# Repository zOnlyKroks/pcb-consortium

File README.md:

# PCB / Circuit Designs

## Support & Issues
If something is broken, unclear, or you need help assembling:
- Open a GitHub Issue
- I’ll try to help when I can

Use at your own risk 🙂

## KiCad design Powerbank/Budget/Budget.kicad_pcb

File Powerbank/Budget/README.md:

# Budget 18650 Powerbank

1S powerbank with 4x 18650 in parallel (about 40-50 Wh with 3.0-3.4 Ah cells). One highly integrated SoC (SW6106) does the charging, the boost and the USB protocols. Built for JLCPCB economic assembly, all parts on the top side.

**Status:** schematic done (ERC 0 violations, netlist matches an independent net spec, 41/41 nets). Board is **placed, not routed** (130 x 90 mm, 2 layers). DRC shows 0 errors other than the unrouted ratsnest, and schematic parity is 0.

## Architecture

| Block | Parts | Notes |
|---|---|---|
| Power SoC | SW6106 (iSmartware) | 4 A switch-mode charger, 18 W synchronous boost, PD3.0 / QC3.0 / AFC / FCP / PE / SFCP out, PD / AFC / FCP in, 4-LED gauge, key input |
| Ports | USB-C (J1) + USB-A (J2) | Each has an AO3420 power-path switch (Q4/Q5) driven by the SoC. USB-C does PD in and out; USB-A is QC/AFC/FCP out only. Micro-B is not used (VBUS_B tied to GND, GATE_B/DPB/DMB open). |
| Power stage | L1 2.2 uH, R1 5 mOhm shunt, C1-C4, C7-C10 | Follows the SW6106 typical application circuit |
| Cell protection | DW01A + 3x FS8205A in parallel | The SW6106 has no cell protection of its own (only a 2.9 V UVLO). Each FS8205A is two FETs in series (about 50 mOhm), so three in parallel are about 17 mOhm, and the DW01A overcurrent trip (about 0.15 V) lands near 9 A. Boost peak at 18 W and 3.0 V is about 6.7 A. |
| Gauge | D1-D4 (charlieplex on LED1-3), D5 fast-charge LED | Press SW1 to show the level |
| NTC | RT1 10k (B3380) | Charge and boost temperature protection. Place it touching a cell. |

Output: 5 V / 3 A, 9 V / 2 A, 12 V / 1.5 A (18 W max). Both ports on at once give 5 V only. Charging: 5 V in = 2.5 A, 9 V / 12 V in = 4 A to the pack (4 A = 0.33 C with 4 cells).

Ground naming: `GND` = PACK- (system ground, after the protection FETs); `CELL_N` = cell stack bottom (DW01A VSS); `VBAT` = cell +.

## Things to check before ordering

- **SW6106 reference circuit.** The typical-application figure in DS008 v2.2 is low resolution. The 100 nF across the shunt, the 22 uF caps at the inductor node / BAT / VOUT, the 1 uF VDRV and the 10 uF VCC are read from the block diagram and figure. Compare them with the official reference design from iSmartware.
- **LED charlieplex order.** LED1-4 are wired per the 4-LED figure in the datasheet. If the bar lights in the wrong order or one LED is dark, swap the polarity of that LED.
- **USB-A part C42570 (JTJ USB-AF-10.0-032).** The footprint is the EasyEDA one: SMD signal pads, through-hole shield legs. Confirm JLC economic assembly accepts it (or hand-solder the legs). The USB-C (C165948) also has through-hole shield legs.
- **Basic vs extended.** Not verified (no JLC parts API access here). The SoC, DW01A, FS8205A, AO3420, inductor, shunt, both USB connectors, holder and switch are almost certainly extended parts (about 3 USD each on economic). The 0603/0805/1206 passives were taken from the V2 BOM, which was checked on 2026-10-24.
- **AO3420 (C358680).** Listed as AOS, marked "not for new designs" at DigiKey. Fallback: MSKSEMI AO3420 C5379109 (18 mOhm), same footprint.
- **CPL rotations** need the usual JLC correction pass (QFN, TSSOP, SOT-23, USB connectors); I did not generate a CPL.
- **Cells.** All four are in parallel with no per-cell protection. Insert cells at the same voltage, same type, and ideally from the same batch. A per-cell fuse is not fitted (budget).

## Board

- 130 x 90 mm, 2 layers, 4 holders on the left (all + up, so VBAT is the top bus and CELL_N the bottom bus), electronics on the right strip, USB ports on the right edge with the gauge LEDs and key beside them.
- Mounting holes: 4x M3 (H1-H4). H1/H2 sit between the holders and the electronics.
- Layers / stackup: 2 copper layers (F.Cu, B.Cu), JLC 1.6 mm FR4, 1 oz (35 um) copper, HASL. B.Cu carries a GND pour (0.3 mm clearance, thermal reliefs, 0.5 mm from the edge). Economic assembly is single-sided, so all parts are on F.Cu and B.Cu is routing + ground.
- Net classes: `Default` 0.25 mm track / 0.2 mm clearance / via 0.6 / 0.3 drill; `Power` (GND, VOUT, VBUS_x switch nodes, SW, BATCSP) 0.8 mm track / via 0.8 / 0.4; `HighCurrent` (VBAT, CELL_N) 2.0 mm track / via 1.0 / 0.5. Use pours where a 2 mm track does not fit.
- Predefined track widths (mm): 0.15, 0.2, 0.25, 0.3, 0.4, 0.5, 0.8, 1.0, 1.5, 2.0, 3.0. Predefined vias (pad / drill): 0.6 / 0.3, 0.8 / 0.4, 1.0 / 0.5.
- Design rules (JLC 2-layer): min clearance 0.1, track 0.15, via 0.6 / 0.3 (0.15 annular), copper to edge 0.3, hole to hole 0.5, silk text 1.0 mm high / 0.15 thick.
- The USB-C footprint has pads 0.1 mm apart (inherent to the part); the J1 pads carry a 0.09 mm local clearance.
- U1: the four thermal vias share pad 41 (GND). Fill the EP with the planned via pattern when routing.

### Routing notes (for later)

- **High current** (about 6-9 A): VBAT bus (holder tops -> R1 -> U1 BAT), CELL_N bus (holder bottoms -> Q1-Q3 S1 pins), Q1-Q3 S2 to GND, and VOUT to Q4/Q5. Use wide copper or pours.
- **GND:** the second layer is meant as a GND plane with vias at U1 EP and the FET sources.
- **SW6106:** keep the SW-L1 loop (L1 above U1) and C1 (BST) tight; C7-C10 close to the VOUT pads.
- **Shunt R1:** route BATCSP/BAT Kelvin from the pads; C3 sits at the pads.
- **Q1-Q3:** the three FS8205A share OD (gate 1) and OC (gate 2) nets from U2; keep those short.
- **DW01A:** R2 (VM) goes to GND, C13 (VCC to CELL_N) right at U2.

## Files

- `Budget.kicad_sch` single-sheet schematic, `Budget.kicad_pcb` placed board
- `lib/Budget.kicad_sym`, `lib/Budget.pretty` project symbols and footprints (SW6106, DW01A, FS8205A, USB, holder, inductor, ...)
- `jlcpcb/BOM-Budget.csv` BOM with LCSC numbers (38 parts, 20 unique)

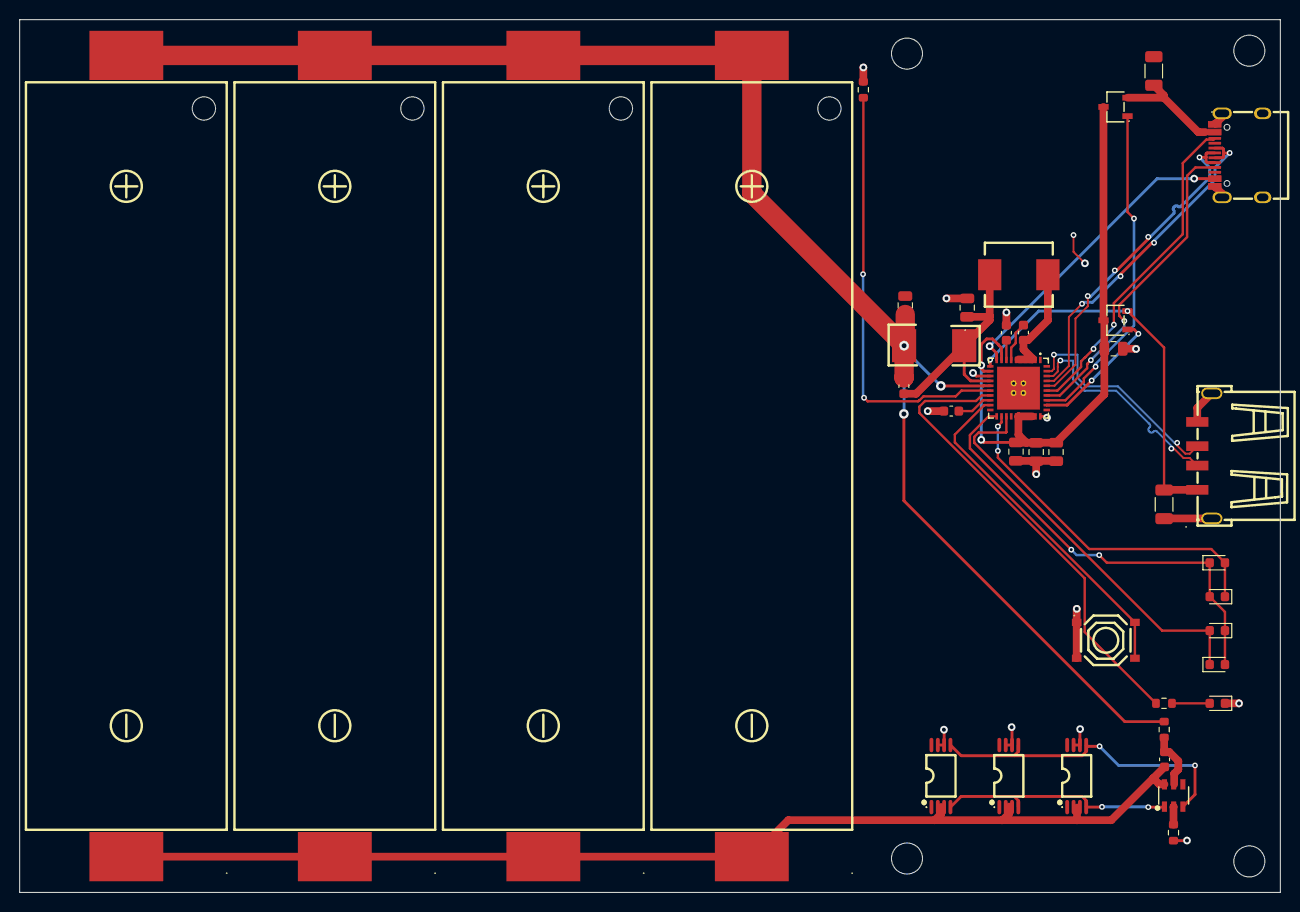
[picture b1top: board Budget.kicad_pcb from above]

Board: 2 copper layers, 130.0 x 90.0 mm, 42 parts (0 on the bottom side), 30 nets.

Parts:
BT1, BT2, BT3, BT4: 18650; BatteryHolder_BH-18650-B1BA002
C1, C3, C13: 100nF; C_0603_1608Metric
C2, C4, C7, C8, C9, C10: 22uF; C_0805_2012Metric
C5: 1uF; C_0603_1608Metric
C6: 10uF; C_0603_1608Metric
C11, C12: 10uF 50V; C_1206_3216Metric
D1, D2, D3, D4: LED; LED_0603_1608Metric
D5: CHG; LED_0603_1608Metric
H1, H2, H3, H4: M3; MountingHole_3.2mm_M3
J1: USB-C; USB-C_SMD-TYPE-C-31-M-12_1
J2: USB-A; USB-A-SMD_JTJ-USB-AF-10.0-032
L1: 2.2uH; L_7.0x6.6_MWSA0603S
Q1, Q2, Q3: FS8205A; TSSOP-8_L4.4-W3.0-P0.65-LS6.4-BL-2
Q4, Q5: AO3420; SOT-23-3_L2.9-W1.6-P1.90-LS2.8-BR
R1: 5mR 1%; RES-SMD_L6.4-W3.2-1
R2, R4: 2.2k; R_0603_1608Metric
R3: 100R; R_0603_1608Metric
RT1: 10k B3380; R_0603_1608Metric
SW1: KEY; SW_TS-1187A_5.1x5.1
U1: SW6106; QFN-40_L6.0-W6.0-P0.50-BL-EP
U2: DW01A; SOT-23-6_L2.9-W1.6-P0.95-LS2.8-BL

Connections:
/A_D+: J2.3 (D+), U1.39 (DPA)
/A_D-: J2.2 (D-), U1.38 (DMA)
/C_D+: J1.A6 (D+), J1.B6 (D+), U1.37 (DPC)
/C_D-: J1.A7 (D-), J1.B7 (D-), U1.36 (DMC)
CELL_N: BT1.2 (-), BT2.2 (-), BT3.2 (-), BT4.2 (-), C13.2, Q1.2 (S1), Q1.3 (S1), Q2.2 (S1), Q2.3 (S1), Q3.2 (S1), Q3.3 (S1), U2.6 (GND)
GND: C2.2, C4.2, C5.1, C6.1, C7.2, C8.2, C9.2, C10.2, C11.2, C12.2, D5.1 (K), J1.1 (GND), J1.2 (GND), J1.3 (GND), J1.4 (GND), J1.A1B12 (GND), J1.B1A12 (GND), J2.4 (GND), J2.5 (SH), J2.6 (SH), Q1.6 (S2), Q1.7 (S2), Q2.6 (S2), Q2.7 (S2), Q3.6 (S2), Q3.7 (S2), R2.2, RT1.1, SW1.1 (A), SW1.3 (A), U1.13 (AGND), U1.30 (VBUS_B), U1.41 (EPAD)
unnamed: C1.2, L1.2, U1.2 (SW), U1.3 (SW), U1.4 (SW), U1.5 (SW), U1.6 (SW)
unnamed: D1.2 (A), D2.1 (K), U1.22 (LED2_SDA)
unnamed: D1.1 (K), D2.2 (A), D3.1 (K), D4.2 (A), U1.21 (LED1_SCK)
unnamed: D3.2 (A), D4.1 (K), U1.23 (LED3_IRQ)
unnamed: D5.2 (A), R4.1
unnamed: J1.A5 (CC1), U1.34 (CC1)
unnamed: J1.B5 (CC2), U1.35 (CC2)
unnamed: C12.1, J2.1 (VBUS), Q5.2 (S), U1.11 (VBUS_A)
unnamed: Q1.4 (G1), Q2.4 (G1), Q3.4 (G1), U2.1 (OD)
unnamed: Q1.5 (G2), Q2.5 (G2), Q3.5 (G2), U2.3 (OC)
unnamed: Q4.1 (G), U1.33 (GATE_C)
unnamed: C11.1, J1.A4B9 (VBUS), J1.B4A9 (VBUS), Q4.2 (S), U1.10 (VBUS_C)
unnamed: Q5.1 (G), U1.32 (GATE_A)
unnamed: C2.1, C3.1, L1.1, R1.1, U1.14 (BATCSP)
unnamed: R4.2, U1.17 (BSET_HLED)
unnamed: C1.1, U1.7 (BST)
unnamed: SW1.2 (B), SW1.4 (B), U1.19 (KEY)
unnamed: RT1.2, U1.16 (NTC)
unnamed: C6.2, U1.18 (VCC)
unnamed: C5.2, U1.8 (VDRV)
unnamed: C13.1, R3.2, U2.5 (VCC)
unnamed: R2.1, U2.2 (VM)
VBAT: BT1.1 (+), BT2.1 (+), BT3.1 (+), BT4.1 (+), C3.2, C4.1, R1.2, R3.1, U1.15 (BAT)
VOUT: C7.1, C8.1, C9.1, C10.1, Q4.3 (D), Q5.3 (D), U1.9 (VOUT_C), U1.12 (VOUT_A), U1.25 (VOUT), U1.26 (VOUT), U1.27 (VOUT), U1.28 (VOUT), U1.29 (VOUT)

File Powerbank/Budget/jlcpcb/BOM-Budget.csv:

Comment,Designator,Footprint,LCSC Part #,Quantity
18650,"BT1,BT2,BT3,BT4",BatteryHolder_BH-18650-B1BA002,C2988620,4
100nF,"C1,C3,C13",C_0603_1608Metric,C14663,3
22uF,"C2,C4,C7,C8,C9,C10",C_0805_2012Metric,C45783,6
1uF,C5,C_0603_1608Metric,C15849,1
10uF,C6,C_0603_1608Metric,C19702,1
10uF 50V,"C11,C12",C_1206_3216Metric,C13585,2
LED,"D1,D2,D3,D4",LED_0603_1608Metric,C2290,4
CHG,D5,LED_0603_1608Metric,C2286,1
USB-C,J1,USB-C_SMD-TYPE-C-31-M-12_1,C165948,1
USB-A,J2,USB-A-SMD_JTJ-USB-AF-10.0-032,C42570,1
2.2uH,L1,L_7.0x6.6_MWSA0603S,C408445,1
FS8205A,"Q1,Q2,Q3",TSSOP-8_L4.4-W3.0-P0.65-LS6.4-BL-2,C14212,3
AO3420,"Q4,Q5",SOT-23-3_L2.9-W1.6-P1.90-LS2.8-BR,C358680,2
5mR 1%,R1,RES-SMD_L6.4-W3.2-1,C2903482,1
2.2k,"R2,R4",R_0603_1608Metric,C4190,2
100R,R3,R_0603_1608Metric,C22775,1
10k B3380,RT1,R_0603_1608Metric,C13564,1
KEY,SW1,SW_TS-1187A_5.1x5.1,C318884,1
SW6106,U1,QFN-40_L6.0-W6.0-P0.50-BL-EP,C406803,1
DW01A,U2,SOT-23-6_L2.9-W1.6-P0.95-LS2.8-BL,C351410,1

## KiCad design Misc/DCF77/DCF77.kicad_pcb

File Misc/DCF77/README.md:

# DCF77 Receiver (self-tuning)

An open-source receiver for the 77.5 kHz DCF77 time signal. Only the ferrite antenna is external, and the board tunes its resonance itself, so a home-wound antenna does not have to hit its inductance exactly. An STM32F103 samples the amplified carrier, demodulates it with a Goertzel filter and decodes the time. The result goes out over USB (virtual COM port), I²C, SPI or UART, with a one-pulse-per-second TICK and the raw pulse.

```
ferrite rod ──┬── tank node ── TLV9062 (x11) ── TLV9062 (x9.2) ── MCU ADC
 (L ≈ 10 mH)  │
              ├── 330 pF fixed C0G
              ├── 10/15/27/56 pF C0G bank via 74HC4066   coarse, 16 steps
              ├── 1SV281 varactor ← MCP4725 DAC          fine
              └── 2.2 pF ← MCU PWM tone                  calibration without a signal
```

**Tuning loop:** sweep the 16 bank codes, climb on the DAC to the carrier peak, then track. Re-sweep on signal loss.

## How far can the antenna be off?

The tuner covers a total tank capacitance of 365–494 pF: 330 pF fixed, 25 pF assumed stray, 0–108 pF bank and about 10–31 pF varactor. At 77.5 kHz that means:

| | Inductance | Versus 10 mH |
|---|---|---|
| Lowest the tuner can reach | 8.5 mH | −15 % |
| Highest the tuner can reach | 11.6 mH | +16 % |

- **Winding:** aim for 10 mH. Inductance goes with turns squared, so the turn count can be off by about ±6 %.
- **Temperature:** drift of about ±1 % uses part of the margin, so staying within 9–11 mH keeps it.
- **Self-capacitance:** the 25 pF stray figure includes the winding's own capacitance. A winding with much more (typically a multi-layer one) shifts the window down. Measure the finished antenna if you can.
- **Q:** the analysis assumes Q = 150. The switches and bias resistor reduce it to 110–135, giving 570–710 Hz bandwidth, enough for the 100/200 ms pulses. The tuner only fixes the frequency, so a low-Q winding still loses signal.
- **Resolution:** the varactor span (21 pF) is larger than the largest coarse step (10 pF), so there are no gaps. One DAC step moves the resonance by about 0.1 Hz.

These figures come from `analysis/frontend.py` (`python3 -I analysis/frontend.py`). The varactor curve is fitted to the 1SV281's distributor figures (8.7 pF at 4 V, ratio 2.0), not its datasheet curve, so treat the window edges as roughly ±1 % uncertain.

## Simulation

The Analog sheet simulates in KiCad (Inspect > Simulator), with models in `models/`. Use `.tran 0.5u 200m` without `uic`. The antenna carrier is keyed like DCF77 (`tred` on J1: 100m for a 0, 200m for a 1). The MCU and power sheets are excluded.

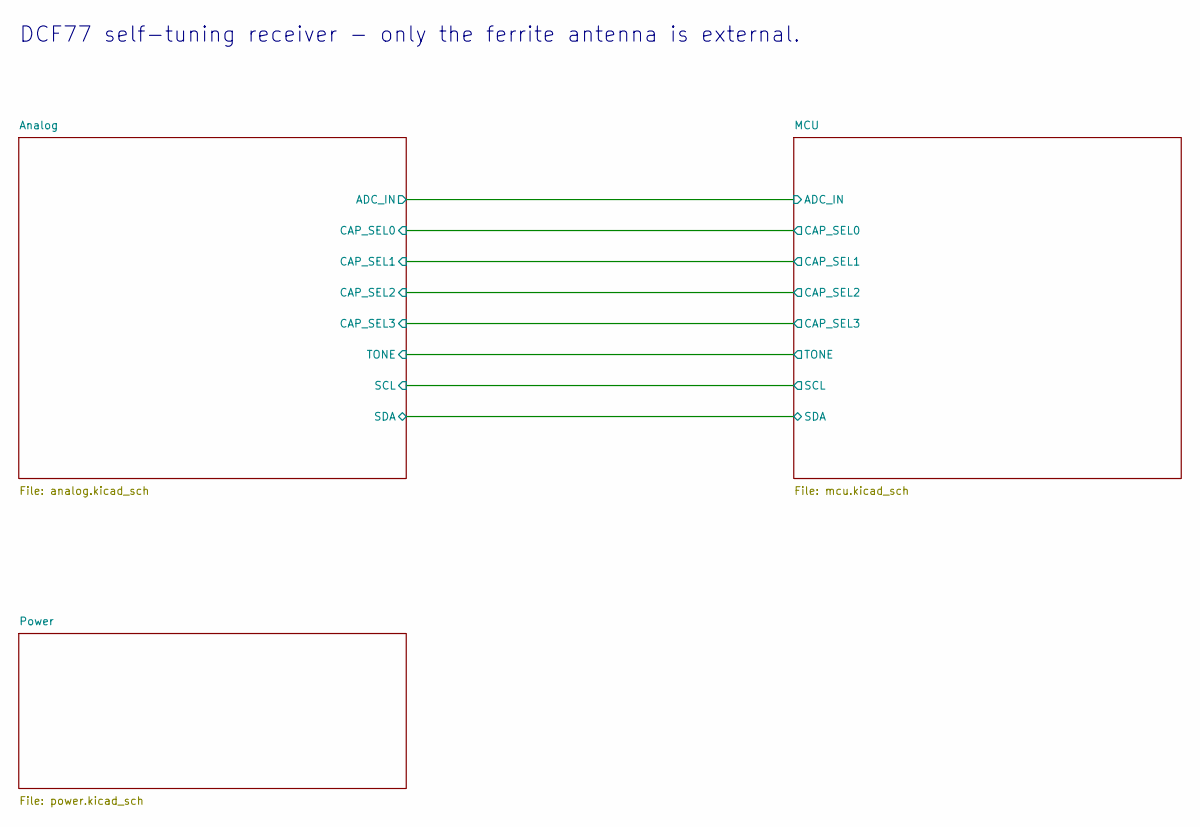
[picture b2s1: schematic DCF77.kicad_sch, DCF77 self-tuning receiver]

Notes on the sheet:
DCF77 self-tuning receiver - only the ferrite antenna is external.

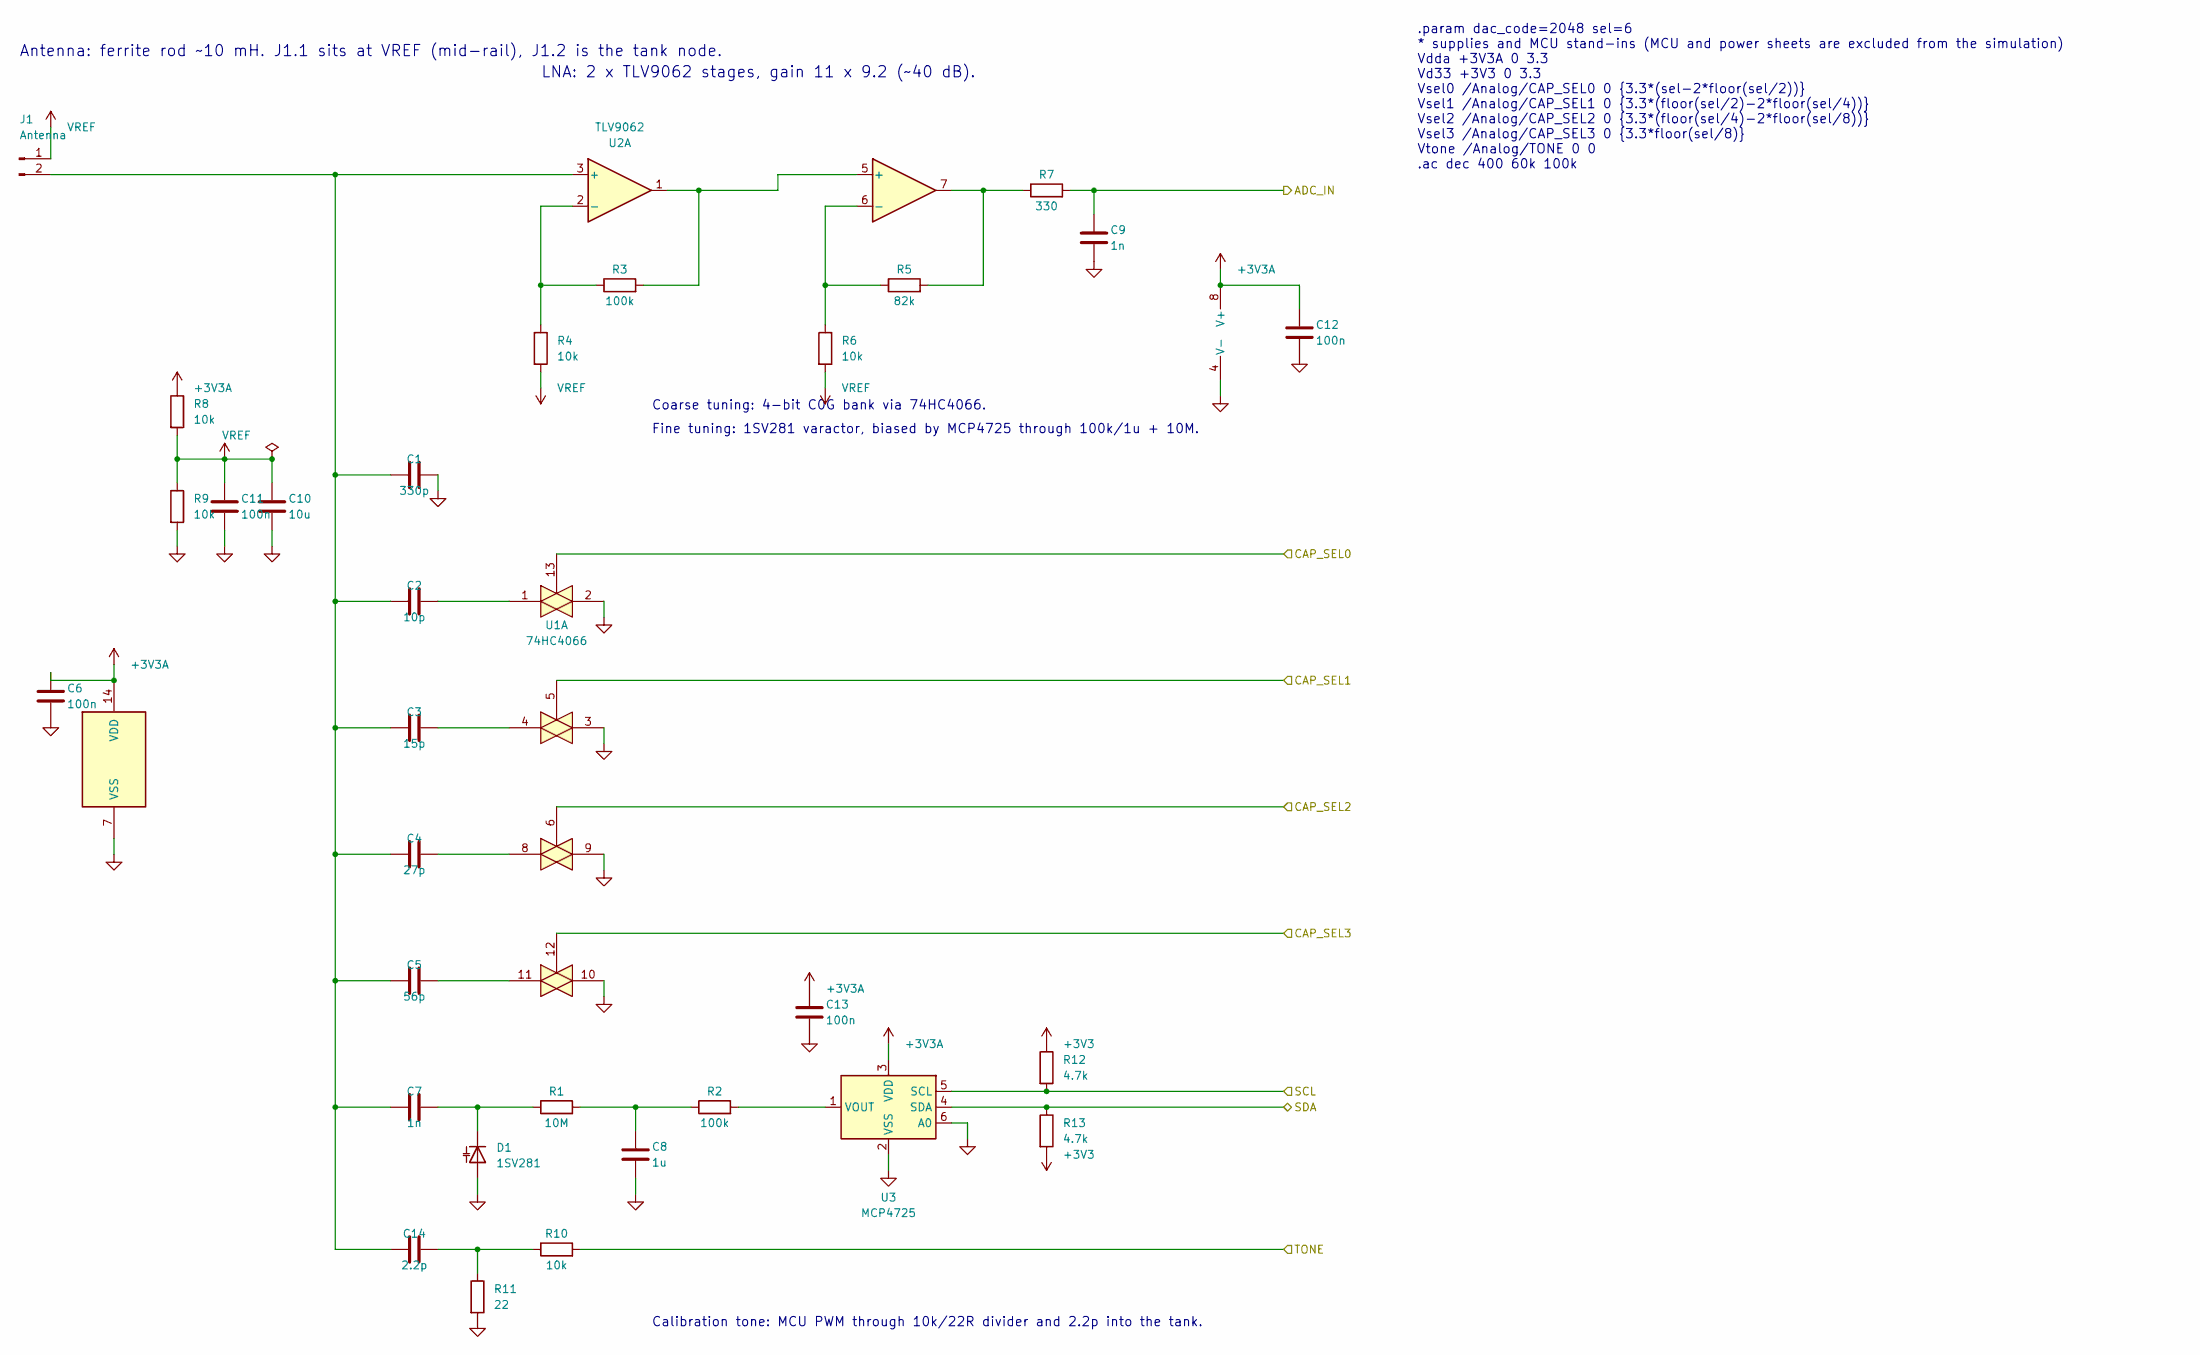
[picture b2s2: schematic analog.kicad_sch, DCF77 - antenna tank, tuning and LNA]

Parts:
C1: 330p; C_0603_1608Metric; LCSC C1664
C2: 10p; C_0603_1608Metric; LCSC C91367
C3: 15p; C_0603_1608Metric; LCSC C1644
C4: 27p; C_0603_1608Metric; LCSC C1656
C5: 56p; C_0603_1608Metric; LCSC C282507
C6, C11, C12, C13: 100n; C_0603_1608Metric; LCSC C14663
C7, C9: 1n; C_0603_1608Metric; LCSC C1636
C8: 1u; C_0603_1608Metric; LCSC C59782
C10: 10u; C_0805_2012Metric; LCSC C15850
C14: 2.2p; C_0603_1608Metric; LCSC C1651
D1: 1SV281; D_SOD-523; LCSC C146317
J1: Antenna; PinHeader_1x02_P2.54mm_Vertical; LCSC C22373836
R1: 10M; R_0603_1608Metric; LCSC C7250
R2, R3: 100k; R_0603_1608Metric; LCSC C25803
R4, R6, R8, R9, R10: 10k; R_0603_1608Metric; LCSC C25804
R5: 82k; R_0603_1608Metric; LCSC C202957
R7: 330; R_0603_1608Metric; LCSC C23138
R11: 22; R_0603_1608Metric; LCSC C23345
R12, R13: 4.7k; R_0603_1608Metric; LCSC C23162
U1: 74HC4066; SOIC-14_3.9x8.7mm_P1.27mm; LCSC C5628
U2: TLV9062; SOIC-8_3.9x4.9mm_P1.27mm; LCSC C398355
U3: MCP4725; SOT-23-6; LCSC C144198

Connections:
+3V3: R12.1, R13.2; also elsewhere on the board
+3V3A: C6.1, C12.1, C13.1, R8.1, U1.14 (VDD), U2.8 (V+), U3.3 (VDD); also elsewhere on the board
/Analog/ADC_IN: C9.1, R7.2; also elsewhere on the board
/Analog/CAP_SEL0: U1.13; also elsewhere on the board
/Analog/CAP_SEL1: U1.5; also elsewhere on the board
/Analog/CAP_SEL2: U1.6; also elsewhere on the board
/Analog/CAP_SEL3: U1.12; also elsewhere on the board
/Analog/SCL: R12.2, U3.5 (SCL); also elsewhere on the board
/Analog/SDA: R13.1, U3.4 (SDA); also elsewhere on the board
/Analog/TONE: R10.2; also elsewhere on the board
GND: C1.2, C6.2, C8.2, C9.2, C10.2, C11.2, C12.2, C13.2, D1.2 (A), R9.2, R11.2, U1.2, U1.3, U1.7 (VSS), U1.9, U1.10, U2.4 (V-), U3.2 (VSS), U3.6 (A0); also elsewhere on the board
unnamed: C2.2, U1.1
unnamed: C3.2, U1.4
unnamed: C4.2, U1.8
unnamed: C5.2, U1.11
unnamed: C8.1, R1.2, R2.1
unnamed: C14.2, R10.1, R11.1
unnamed: C7.2, D1.1 (K), R1.1
unnamed: C1.1, C2.1, C3.1, C4.1, C5.1, C7.1, C14.1, J1.2, U2.3 (+)
unnamed: R5.2, R7.1, U2.7
unnamed: R3.1, R4.1, U2.2 (-)
unnamed: R3.2, U2.1, U2.5 (+)
unnamed: R5.1, R6.1, U2.6 (-)
unnamed: R2.2, U3.1 (VOUT)
VREF: C10.1, C11.1, J1.1, R4.2, R6.2, R8.2, R9.1

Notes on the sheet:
Antenna: ferrite rod ~10 mH. J1.1 sits at VREF (mid-rail), J1.2 is the tank node.
Calibration tone: MCU PWM through 10k/22R divider and 2.2p into the tank.
.param dac_code=2048 sel=6 * supplies and MCU stand-ins (MCU and power sheets are excluded from the simulation) Vdda +3V3A 0 3.3 Vd33 +3V3 0 3.3 Vsel0 /Analog/CAP_SEL0 0 {3.3*(sel-2*floor(sel/2))} Vsel1 /Analog/CAP_SEL1 0 {3.3*(floor(sel/2)-2*floor(sel/4))} Vsel2 /Analog/CAP_SEL2 0 {3.3*(floor(sel/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
Fine tuning: 1SV281 varactor, biased by MCP4725 through 100k/1u + 10M.
Coarse tuning: 4-bit C0G bank via 74HC4066.
LNA: 2 x TLV9062 stages, gain 11 x 9.2 (~40 dB).

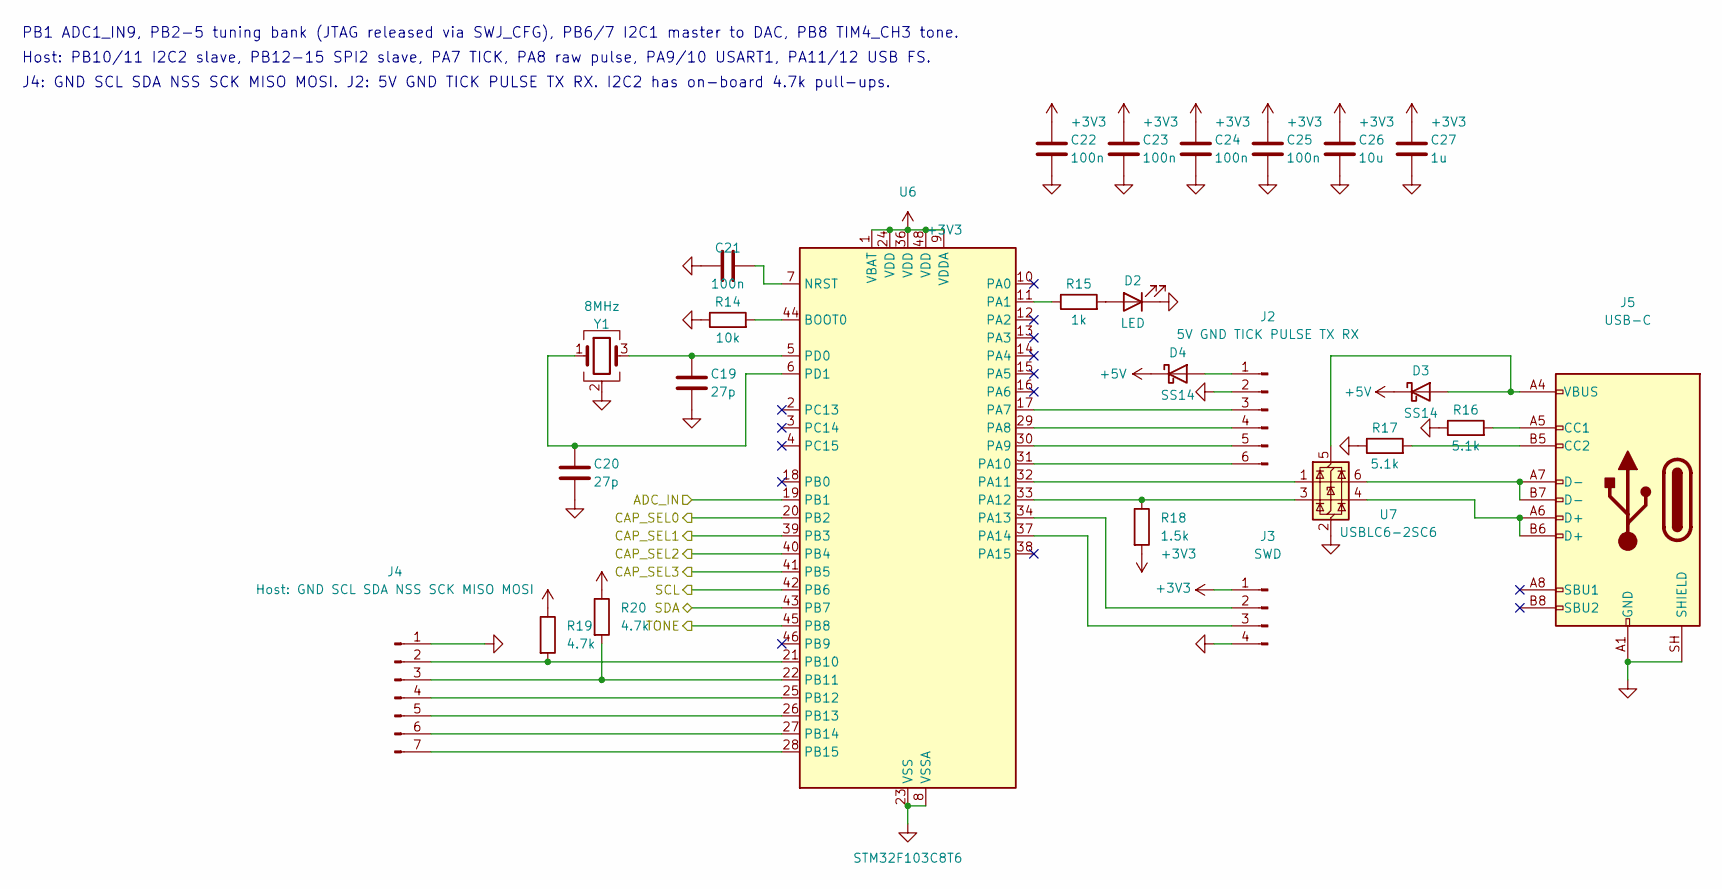
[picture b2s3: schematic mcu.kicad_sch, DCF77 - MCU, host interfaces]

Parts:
C19, C20: 27p; C_0603_1608Metric; LCSC C1656
C21, C22, C23, C24, C25: 100n; C_0603_1608Metric; LCSC C14663
C26: 10u; C_0805_2012Metric; LCSC C15850
C27: 1u; C_0603_1608Metric; LCSC C59782
D2: LED; LED_0603_1608Metric; LCSC C2286
D3, D4: SS14; D_SMA; LCSC C2480
J2: 5V GND TICK PULSE TX RX; PinHeader_1x06_P2.54mm_Vertical; LCSC C22373836
J3: SWD; PinHeader_1x04_P2.54mm_Vertical; LCSC C22373836
J4: Host: GND SCL SDA NSS SCK MISO MOSI; PinHeader_1x07_P2.54mm_Vertical; LCSC C22373836
J5: USB-C; USB_C_Receptacle_HRO_TYPE-C-31-M-12; LCSC C165948
R14: 10k; R_0603_1608Metric; LCSC C25804
R15: 1k; R_0603_1608Metric; LCSC C21190
R16, R17: 5.1k; R_0603_1608Metric; LCSC C23186
R18: 1.5k; R_0603_1608Metric; LCSC C22843
R19, R20: 4.7k; R_0603_1608Metric; LCSC C23162
U6: STM32F103C8T6; LQFP-48_7x7mm_P0.5mm; LCSC C8734
U7: USBLC6-2SC6; SOT-23-6; LCSC C7519
Y1: 8MHz; Crystal_SMD_3225-4Pin_3.2x2.5mm; LCSC C2682774

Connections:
+3V3: C22.1, C23.1, C24.1, C25.1, C26.1, C27.1, J3.1, R18.2, R19.1, R20.1, U6.1 (VBAT), U6.9 (VDDA), U6.24 (VDD), U6.36 (VDD), U6.48 (VDD); also elsewhere on the board
+5V: D3.1 (K), D4.1 (K); also elsewhere on the board
/Analog/ADC_IN: U6.19 (PB1); also elsewhere on the board
/Analog/CAP_SEL0: U6.20 (PB2); also elsewhere on the board
/Analog/CAP_SEL1: U6.39 (PB3); also elsewhere on the board
/Analog/CAP_SEL2: U6.40 (PB4); also elsewhere on the board
/Analog/CAP_SEL3: U6.41 (PB5); also elsewhere on the board
/Analog/SCL: U6.42 (PB6); also elsewhere on the board
/Analog/SDA: U6.43 (PB7); also elsewhere on the board
/Analog/TONE: U6.45 (PB8); also elsewhere on the board
GND: C19.2, C20.2, C21.1, C22.2, C23.2, C24.2, C25.2, C26.2, C27.2, D2.1 (K), J2.2, J3.4, J4.1, J5.A1 (GND), J5.A12 (GND), J5.B1 (GND), J5.B12 (GND), J5.SH (SHIELD), R14.1, R16.1, R17.1, U6.8 (VSSA), U6.23 (VSS), U6.35 (VSS), U6.47 (VSS), U7.2 (GND), Y1.2 (G), Y1.4 (G); also elsewhere on the board
unnamed: D2.2 (A), R15.2
unnamed: D3.2 (A), J5.A4 (VBUS), J5.A9 (VBUS), J5.B4 (VBUS), J5.B9 (VBUS), U7.5 (VBUS)
unnamed: D4.2 (A), J2.1
unnamed: J2.3, U6.17 (PA7)
unnamed: J2.4, U6.29 (PA8)
unnamed: J2.5, U6.30 (PA9)
unnamed: J2.6, U6.31 (PA10)
unnamed: J3.2, U6.34 (PA13)
unnamed: J3.3, U6.37 (PA14)
unnamed: J4.2, R19.2, U6.21 (PB10)
unnamed: J4.3, R20.2, U6.22 (PB11)
unnamed: J4.4, U6.25 (PB12)
unnamed: J4.5, U6.26 (PB13)
unnamed: J4.6, U6.27 (PB14)
unnamed: J4.7, U6.28 (PB15)
unnamed: J5.A5 (CC1), R16.2
unnamed: J5.B5 (CC2), R17.2
unnamed: J5.A6 (D+), J5.B6 (D+), U7.4 (I/O2)
unnamed: J5.A7 (D-), J5.B7 (D-), U7.6 (I/O1)
unnamed: R14.2, U6.44 (BOOT0)
unnamed: C21.2, U6.7 (NRST)
unnamed: R15.1, U6.11 (PA1)
unnamed: U6.32 (PA11), U7.1 (I/O1)
unnamed: R18.1, U6.33 (PA12), U7.3 (I/O2)
unnamed: C19.1, U6.5 (PD0), Y1.3
unnamed: C20.1, U6.6 (PD1), Y1.1

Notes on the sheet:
PB1 ADC1_IN9, PB2-5 tuning bank (JTAG released via SWJ_CFG), PB6/7 I2C1 master to DAC, PB8 TIM4_CH3 tone.
J4: GND SCL SDA NSS SCK MISO MOSI. J2: 5V GND TICK PULSE TX RX. I2C2 has on-board 4.7k pull-ups.
Host: PB10/11 I2C2 slave, PB12-15 SPI2 slave, PA7 TICK, PA8 raw pulse, PA9/10 USART1, PA11/12 USB FS.

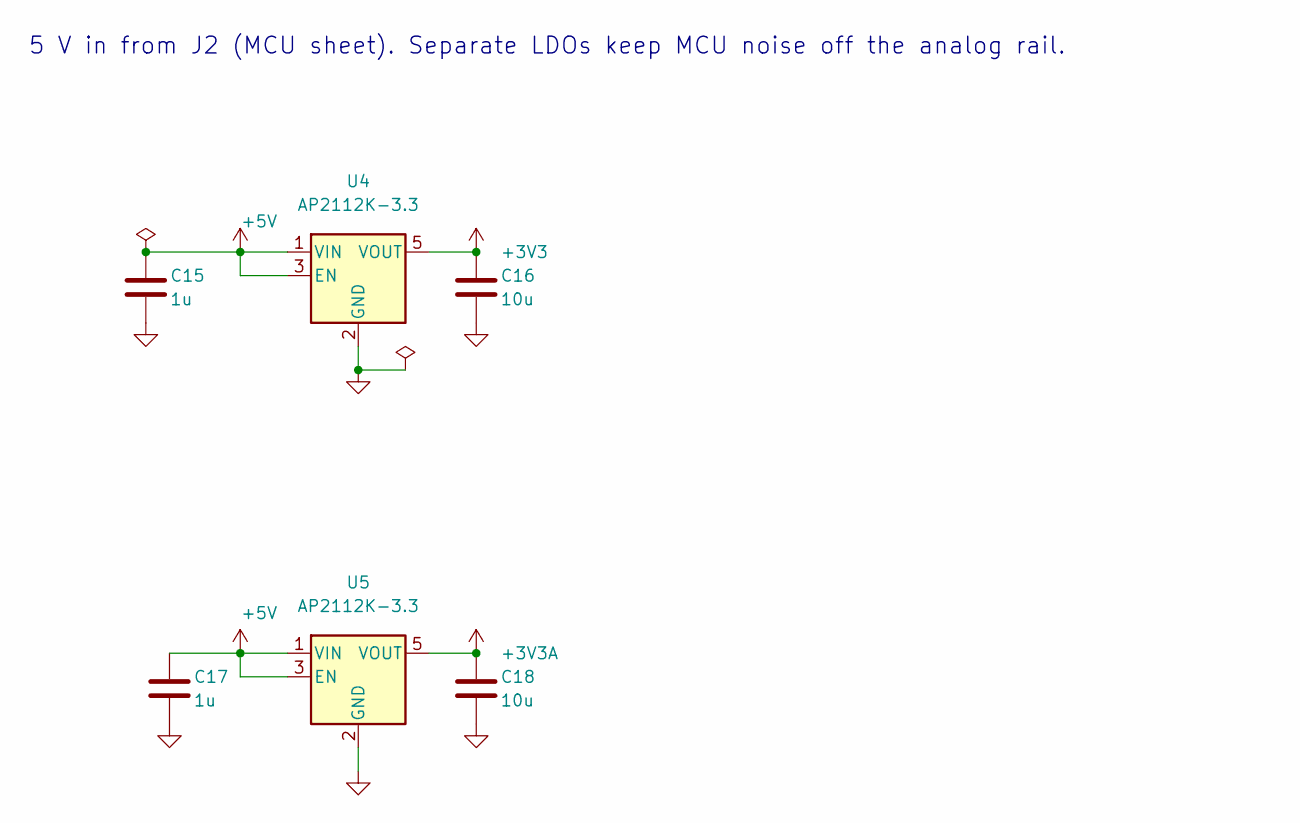
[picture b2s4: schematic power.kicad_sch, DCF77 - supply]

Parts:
C15, C17: 1u; C_0603_1608Metric; LCSC C59782
C16, C18: 10u; C_0805_2012Metric; LCSC C15850
U4, U5: AP2112K-3.3; SOT-23-5; LCSC C51118

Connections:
+3V3: C16.1, U4.5 (VOUT); also elsewhere on the board
+3V3A: C18.1, U5.5 (VOUT); also elsewhere on the board
+5V: C15.1, C17.1, U4.1 (VIN), U4.3 (EN), U5.1 (VIN), U5.3 (EN); also elsewhere on the board
GND: C15.2, C16.2, C17.2, C18.2, U4.2 (GND), U5.2 (GND); also elsewhere on the board

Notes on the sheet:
5 V in from J2 (MCU sheet). Separate LDOs keep MCU noise off the analog rail.

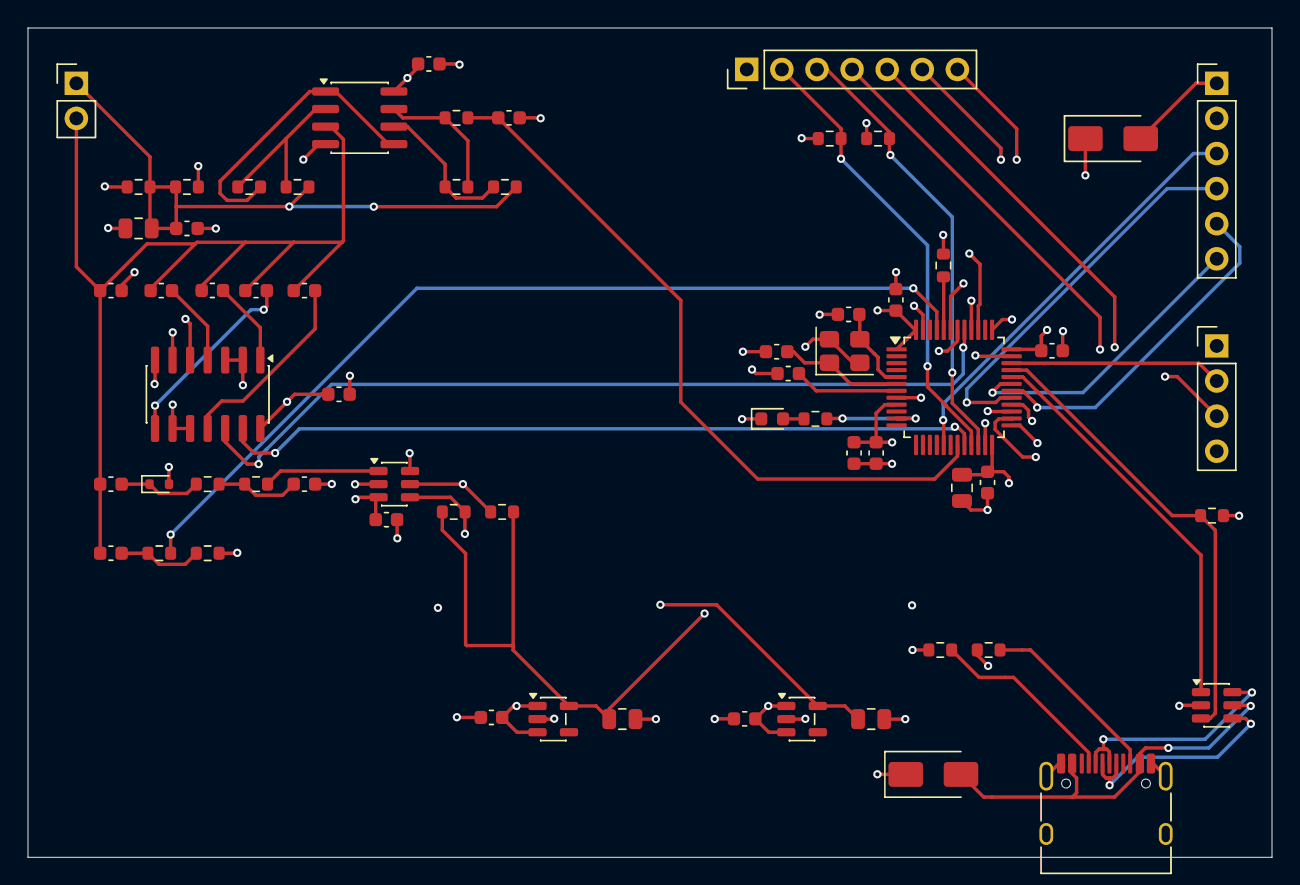
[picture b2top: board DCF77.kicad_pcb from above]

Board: 4 copper layers, 90.0 x 60.0 mm, 64 parts (0 on the bottom side), 52 nets.

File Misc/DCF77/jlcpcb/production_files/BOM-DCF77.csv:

Comment,Designator,Footprint,LCSC,Quantity
1.5k,R18,R_0603_1608Metric,C22843,1
100k,"R2,R3",R_0603_1608Metric,C25803,2
100n,"C11,C12,C13,C21,C22,C23,C24,C25,C6",C_0603_1608Metric,C14663,9
10M,R1,R_0603_1608Metric,C7250,1
10k,"R10,R14,R4,R6,R8,R9",R_0603_1608Metric,C25804,6
10p,C2,C_0603_1608Metric,C1634,1
10u,"C10,C16,C18,C26",C_0805_2012Metric,C15850,4
15p,C3,C_0603_1608Metric,C1644,1
1SV281,D1,D_SOD-523,C146317,1
1k,R15,R_0603_1608Metric,C21190,1
1n,"C7,C9",C_0603_1608Metric,C1588,2
1u,"C15,C17,C27,C8",C_0603_1608Metric,C15849,4
2.2p,C14,C_0603_1608Metric,C1651,1
22,R11,R_0603_1608Metric,C23345,1
27p,"C19,C20,C4",C_0603_1608Metric,C107045,3
330,R7,R_0603_1608Metric,C23138,1
330p,C1,C_0603_1608Metric,C1664,1
4.7k,"R12,R13,R19,R20",R_0603_1608Metric,C23162,4
5.1k,"R16,R17",R_0603_1608Metric,C23186,2
56p,C5,C_0603_1608Metric,C39148,1
5V GND TICK PULSE TX RX,J2,PinHeader_1x06_P2.54mm_Vertical,C22373836,1
74HC4066,U1,SOIC-14_3.9x8.7mm_P1.27mm,C5628,1
82k,R5,R_0603_1608Metric,C23254,1
8MHz,Y1,Crystal_SMD_3225-4Pin_3.2x2.5mm,C2682774,1
AP2112K-3.3,"U4,U5",SOT-23-5,C51118,2
Antenna,J1,PinHeader_1x02_P2.54mm_Vertical,C22373836,1
Host: GND SCL SDA NSS SCK MISO MOSI,J4,PinHeader_1x07_P2.54mm_Vertical,C22373836,1
LED,D2,LED_0603_1608Metric,C2286,1
MCP4725,U3,SOT-23-6,C144198,1
SS14,"D3,D4",D_SMA,C2480,2
STM32F103C8T6,U6,LQFP-48_7x7mm_P0.5mm,C8734,1
SWD,J3,PinHeader_1x04_P2.54mm_Vertical,C22373836,1
TLV9062,U2,SOIC-8_3.9x4.9mm_P1.27mm,C398355,1
USB-C,J5,USB_C_Receptacle_HRO_TYPE-C-31-M-12,C165948,1
USBLC6-2SC6,U7,SOT-23-6,C7519,1
